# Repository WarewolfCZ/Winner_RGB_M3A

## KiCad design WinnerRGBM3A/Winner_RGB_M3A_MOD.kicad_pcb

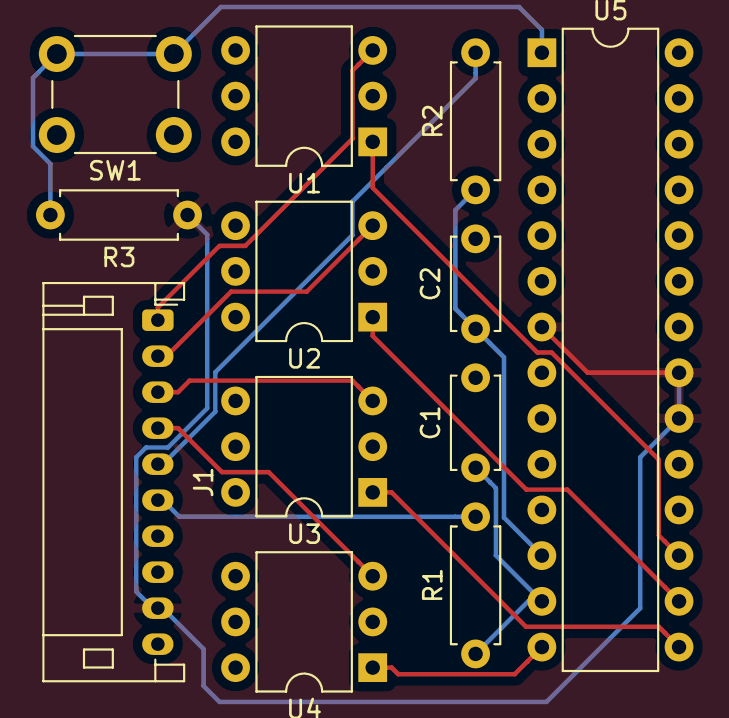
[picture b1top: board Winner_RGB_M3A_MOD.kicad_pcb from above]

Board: 2 copper layers, 12 parts (0 on the bottom side), 15 nets.

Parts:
C1, C2: 4.7nF; C_Disc_D5.0mm_W2.5mm_P5.00mm
J1: Conn_01x10; JST_PH_S10B-PH-K_1x10_P2.00mm_Horizontal
R1, R2: 330k; R_Axial_DIN0207_L6.3mm_D2.5mm_P7.62mm_Horizontal
R3: 10k; R_Axial_DIN0207_L6.3mm_D2.5mm_P7.62mm_Horizontal
SW1: SW_Push; SW_PUSH_6mm_H5mm
U1, U2, U3, U4: MOC3062M; DIP-6_W7.62mm
U5: ATmega8-16PU; DIP-28_W7.62mm

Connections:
/5V: J1.9, R3.1, U5.7, U5.20, U5.21
/GND: C1.2, C2.2, J1.10, SW1.1, U1.2, U2.2, U3.2, U4.2, U5.8, U5.22
unnamed: C1.1, R1.1, U5.13
unnamed: C2.1, R2.1, U5.12
unnamed: J1.1, U1.3
unnamed: J1.2, U2.3
unnamed: J1.3, U3.3
unnamed: J1.4, U4.3
unnamed: J1.5, R2.2
unnamed: J1.6, R1.2
unnamed: R3.2, SW1.2, U5.1
unnamed: U1.1, U5.17
unnamed: U2.1, U5.16
unnamed: U3.1, U5.15
unnamed: U4.1, U5.14

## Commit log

2019-12-30 files added
2020-01-12 firmware working, except commands
2020-01-12 Serial interface
2020-01-13 fixes, optimalizations
2020-01-13 readme fixed
2020-01-13 added photos
2020-01-13 changed project structure
